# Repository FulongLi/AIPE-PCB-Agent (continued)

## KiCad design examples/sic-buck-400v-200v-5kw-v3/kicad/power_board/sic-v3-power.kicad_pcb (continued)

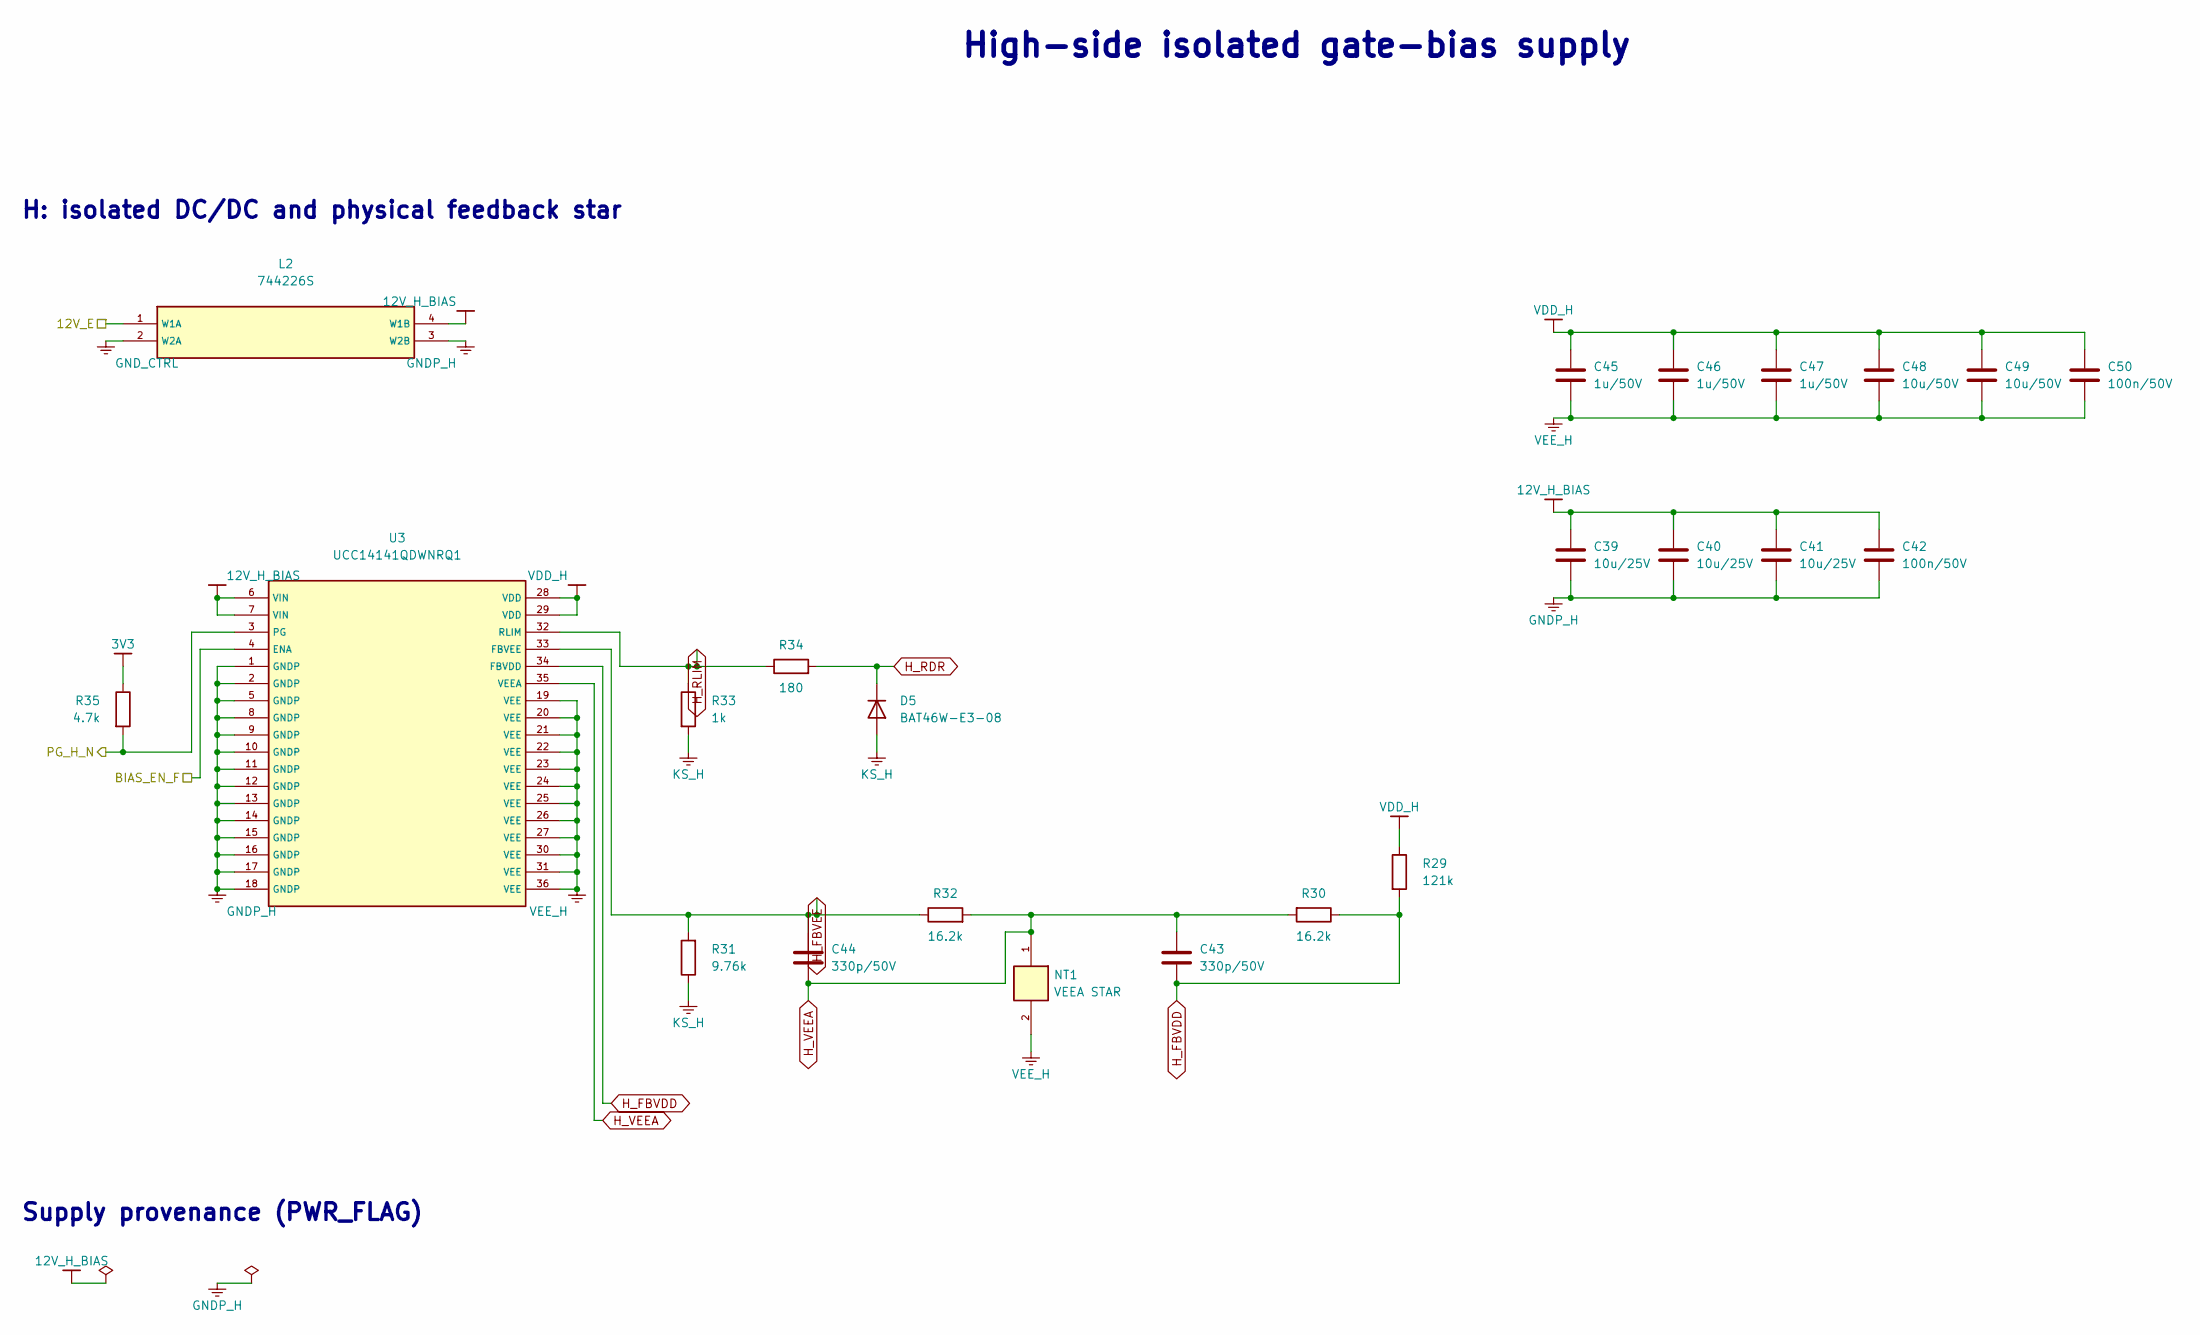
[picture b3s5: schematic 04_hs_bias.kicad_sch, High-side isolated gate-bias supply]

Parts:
C39, C40, C41: 10u/25V; C_1210_3225Metric
C42, C50: 100n/50V; C_0603_1608Metric
C43, C44: 330p/50V; C_0603_1608Metric
C45, C46, C47: 1u/50V; C_0805_2012Metric
C48, C49: 10u/50V; C_1210_3225Metric
D5: BAT46W-E3-08; D_SOD-123
L2: 744226S; L_CommonMode_Wuerth_WE-SL2
NT1: VEEA STAR; NetTie-2_SMD_Pad0.5mm
R29: 121k; R_0603_1608Metric
R30, R32: 16.2k; R_0603_1608Metric
R31: 9.76k; R_0603_1608Metric
R33: 1k; R_1206_3216Metric
R34: 180; R_1206_3216Metric
R35: 4.7k; R_0603_1608Metric
U3: UCC14141QDWNRQ1; V3_UCC14141_DWN

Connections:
3V3: R35.1; also elsewhere on the board
12V_E: L2.1 (W1A); also elsewhere on the board
12V_H_BIAS: C39.1, C40.1, C41.1, C42.1, L2.4 (W1B), U3.6 (VIN), U3.7 (VIN)
BIAS_EN_F: U3.4 (ENA); also elsewhere on the board
GNDP_H: C39.2, C40.2, C41.2, C42.2, L2.3 (W2B), U3.1 (GNDP), U3.2 (GNDP), U3.5 (GNDP), U3.8 (GNDP), U3.9 (GNDP), U3.10 (GNDP), U3.11 (GNDP), U3.12 (GNDP), U3.13 (GNDP), U3.14 (GNDP), U3.15 (GNDP), U3.16 (GNDP), U3.17 (GNDP), U3.18 (GNDP)
GND_CTRL: L2.2 (W2A); also elsewhere on the board
H_FBVDD: C43.1, R29.2, R30.1, U3.34 (FBVDD)
H_FBVEE: C44.1, R31.2, R32.1, U3.33 (FBVEE)
H_RDR: D5.1 (K), R34.2
H_RLIM: R33.1, R34.1, U3.32 (RLIM)
H_VEEA: C43.2, C44.2, NT1.1, R30.2, R32.2, U3.35 (VEEA)
KS_H: D5.2 (A), R31.1, R33.2; also elsewhere on the board
PG_H_N: R35.2, U3.3 (PG); also elsewhere on the board
VDD_H: C45.1, C46.1, C47.1, C48.1, C49.1, C50.1, R29.1, U3.28 (VDD), U3.29 (VDD); also elsewhere on the board
VEE_H: C45.2, C46.2, C47.2, C48.2, C49.2, C50.2, NT1.2, U3.19 (VEE), U3.20 (VEE), U3.21 (VEE), U3.22 (VEE), U3.23 (VEE), U3.24 (VEE), U3.25 (VEE), U3.26 (VEE), U3.27 (VEE), U3.30 (VEE), U3.31 (VEE), U3.36 (VEE); also elsewhere on the board

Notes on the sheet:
High-side isolated gate-bias supply
H: isolated DC/DC and physical feedback star
Supply provenance (PWR_FLAG)

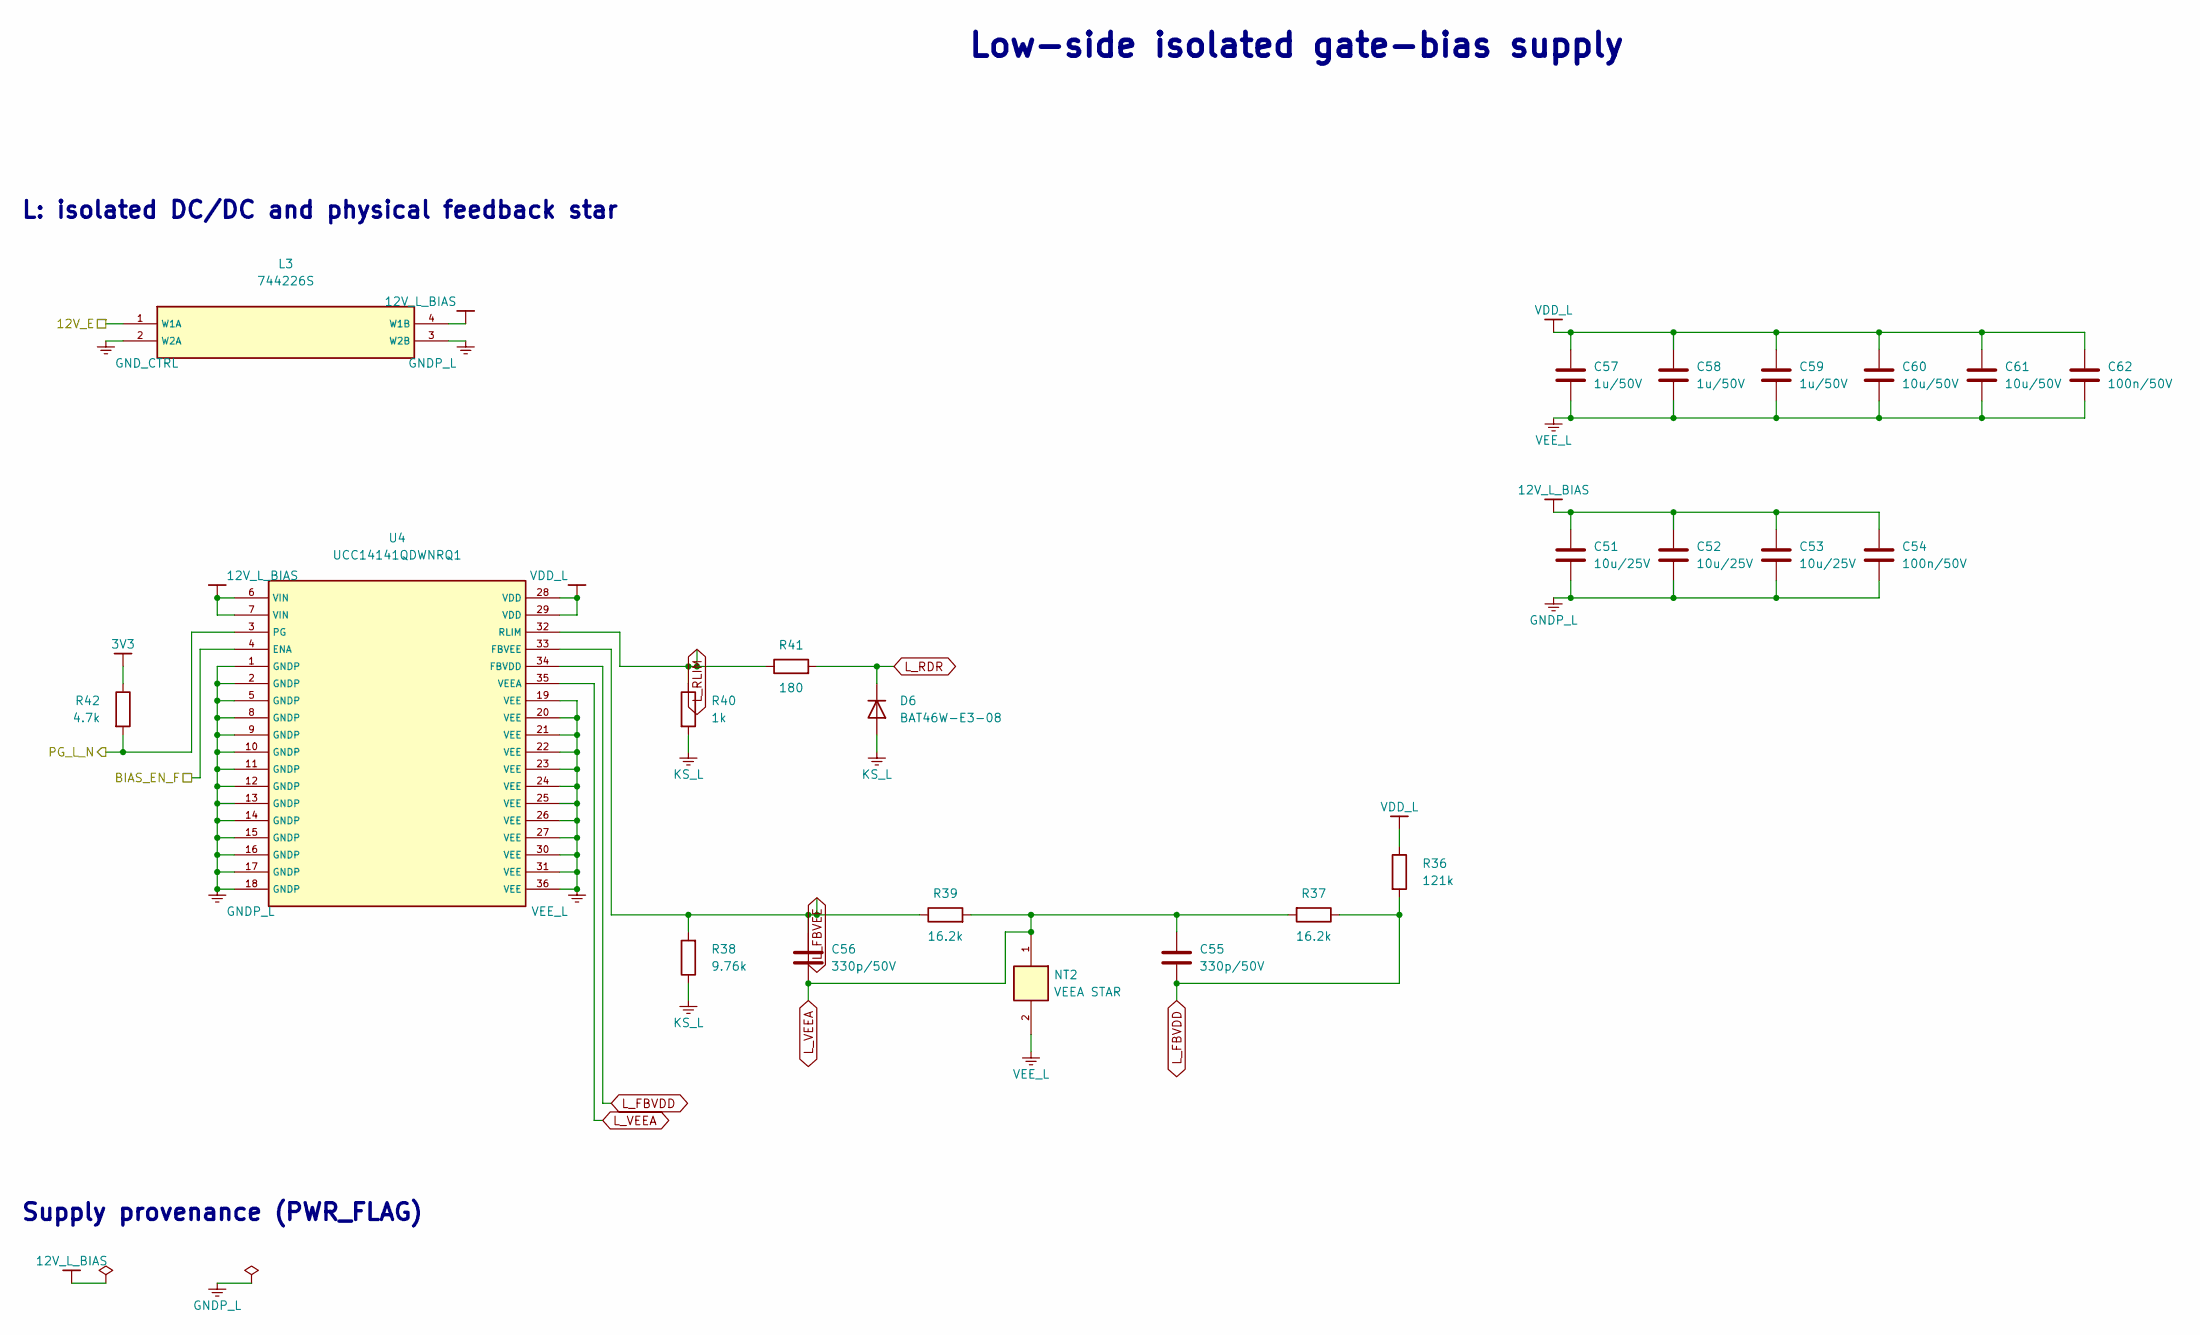
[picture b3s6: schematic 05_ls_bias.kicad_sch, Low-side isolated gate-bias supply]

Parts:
C51, C52, C53: 10u/25V; C_1210_3225Metric
C54, C62: 100n/50V; C_0603_1608Metric
C55, C56: 330p/50V; C_0603_1608Metric
C57, C58, C59: 1u/50V; C_0805_2012Metric
C60, C61: 10u/50V; C_1210_3225Metric
D6: BAT46W-E3-08; D_SOD-123
L3: 744226S; L_CommonMode_Wuerth_WE-SL2
NT2: VEEA STAR; NetTie-2_SMD_Pad0.5mm
R36: 121k; R_0603_1608Metric
R37, R39: 16.2k; R_0603_1608Metric
R38: 9.76k; R_0603_1608Metric
R40: 1k; R_1206_3216Metric
R41: 180; R_1206_3216Metric
R42: 4.7k; R_0603_1608Metric
U4: UCC14141QDWNRQ1; V3_UCC14141_DWN

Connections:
3V3: R42.1; also elsewhere on the board
12V_E: L3.1 (W1A); also elsewhere on the board
12V_L_BIAS: C51.1, C52.1, C53.1, C54.1, L3.4 (W1B), U4.6 (VIN), U4.7 (VIN)
BIAS_EN_F: U4.4 (ENA); also elsewhere on the board
GNDP_L: C51.2, C52.2, C53.2, C54.2, L3.3 (W2B), U4.1 (GNDP), U4.2 (GNDP), U4.5 (GNDP), U4.8 (GNDP), U4.9 (GNDP), U4.10 (GNDP), U4.11 (GNDP), U4.12 (GNDP), U4.13 (GNDP), U4.14 (GNDP), U4.15 (GNDP), U4.16 (GNDP), U4.17 (GNDP), U4.18 (GNDP)
GND_CTRL: L3.2 (W2A); also elsewhere on the board
KS_L: D6.2 (A), R38.1, R40.2; also elsewhere on the board
L_FBVDD: C55.1, R36.2, R37.1, U4.34 (FBVDD)
L_FBVEE: C56.1, R38.2, R39.1, U4.33 (FBVEE)
L_RDR: D6.1 (K), R41.2
L_RLIM: R40.1, R41.1, U4.32 (RLIM)
L_VEEA: C55.2, C56.2, NT2.1, R37.2, R39.2, U4.35 (VEEA)
PG_L_N: R42.2, U4.3 (PG); also elsewhere on the board
VDD_L: C57.1, C58.1, C59.1, C60.1, C61.1, C62.1, R36.1, U4.28 (VDD), U4.29 (VDD); also elsewhere on the board
VEE_L: C57.2, C58.2, C59.2, C60.2, C61.2, C62.2, NT2.2, U4.19 (VEE), U4.20 (VEE), U4.21 (VEE), U4.22 (VEE), U4.23 (VEE), U4.24 (VEE), U4.25 (VEE), U4.26 (VEE), U4.27 (VEE), U4.30 (VEE), U4.31 (VEE), U4.36 (VEE); also elsewhere on the board

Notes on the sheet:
Low-side isolated gate-bias supply
L: isolated DC/DC and physical feedback star
Supply provenance (PWR_FLAG)

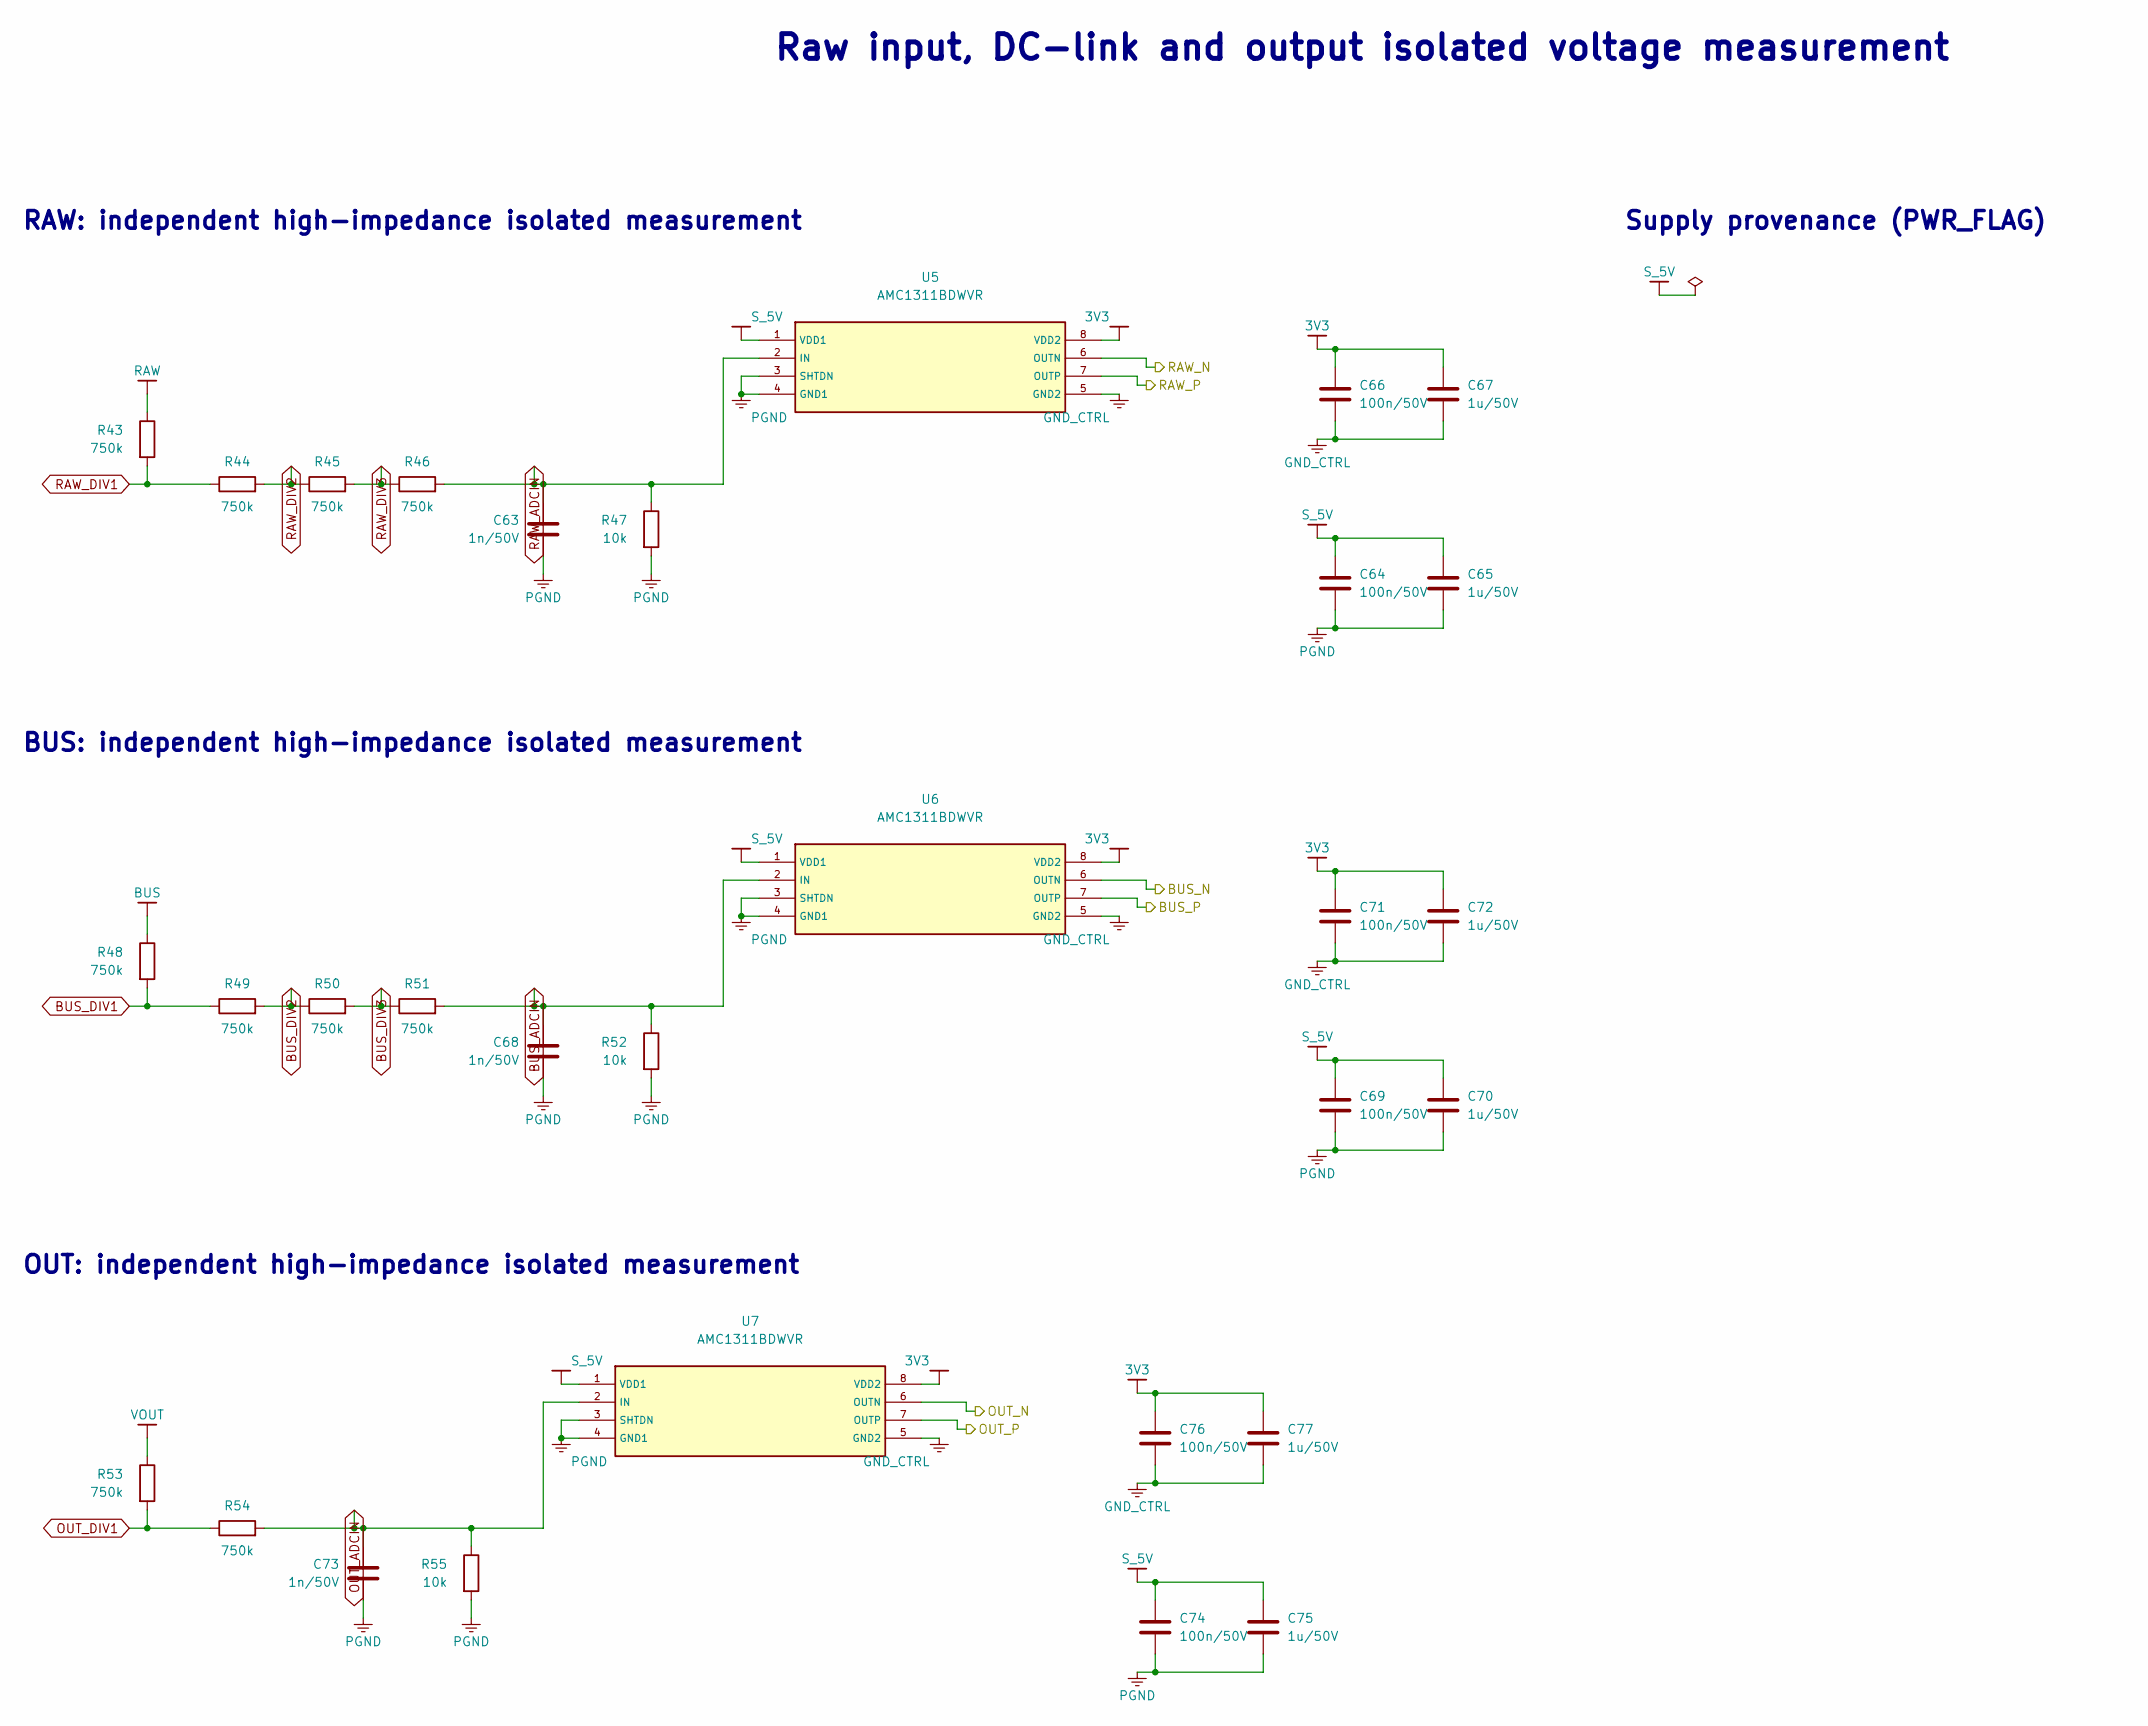
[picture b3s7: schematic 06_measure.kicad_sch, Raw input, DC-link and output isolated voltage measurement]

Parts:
C63, C68, C73: 1n/50V; C_0603_1608Metric
C64, C66, C69, C71, C74, C76: 100n/50V; C_0603_1608Metric
C65, C67, C70, C72, C75, C77: 1u/50V; C_0805_2012Metric
R43, R44, R45, R46, R48, R49, R50, R51, R53, R54: 750k; R_1206_3216Metric
R47, R52, R55: 10k; R_0603_1608Metric
U5, U6, U7: AMC1311BDWVR; V3_AMC1311_DWV

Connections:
3V3: C66.1, C67.1, C71.1, C72.1, C76.1, C77.1, U5.8 (VDD2), U6.8 (VDD2), U7.8 (VDD2); also elsewhere on the board
BUS: R48.1; also elsewhere on the board
BUS_ADCIN: C68.1, R51.2, R52.1, U6.2 (IN)
BUS_DIV1: R48.2, R49.1
BUS_DIV2: R49.2, R50.1
BUS_DIV3: R50.2, R51.1
BUS_N: U6.6 (OUTN); also elsewhere on the board
BUS_P: U6.7 (OUTP); also elsewhere on the board
GND_CTRL: C66.2, C67.2, C71.2, C72.2, C76.2, C77.2, U5.5 (GND2), U6.5 (GND2), U7.5 (GND2); also elsewhere on the board
OUT_ADCIN: C73.1, R54.2, R55.1, U7.2 (IN)
OUT_DIV1: R53.2, R54.1
OUT_N: U7.6 (OUTN); also elsewhere on the board
OUT_P: U7.7 (OUTP); also elsewhere on the board
PGND: C63.2, C64.2, C65.2, C68.2, C69.2, C70.2, C73.2, C74.2, C75.2, R47.2, R52.2, R55.2, U5.3 (SHTDN), U5.4 (GND1), U6.3 (SHTDN), U6.4 (GND1), U7.3 (SHTDN), U7.4 (GND1); also elsewhere on the board
RAW: R43.1; also elsewhere on the board
RAW_ADCIN: C63.1, R46.2, R47.1, U5.2 (IN)
RAW_DIV1: R43.2, R44.1
RAW_DIV2: R44.2, R45.1
RAW_DIV3: R45.2, R46.1
RAW_N: U5.6 (OUTN); also elsewhere on the board
RAW_P: U5.7 (OUTP); also elsewhere on the board
S_5V: C64.1, C65.1, C69.1, C70.1, C74.1, C75.1, U5.1 (VDD1), U6.1 (VDD1), U7.1 (VDD1); also elsewhere on the board
VOUT: R53.1; also elsewhere on the board

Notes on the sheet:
Raw input, DC-link and output isolated voltage measurement
RAW: independent high-impedance isolated measurement
BUS: independent high-impedance isolated measurement
OUT: independent high-impedance isolated measurement
Supply provenance (PWR_FLAG)

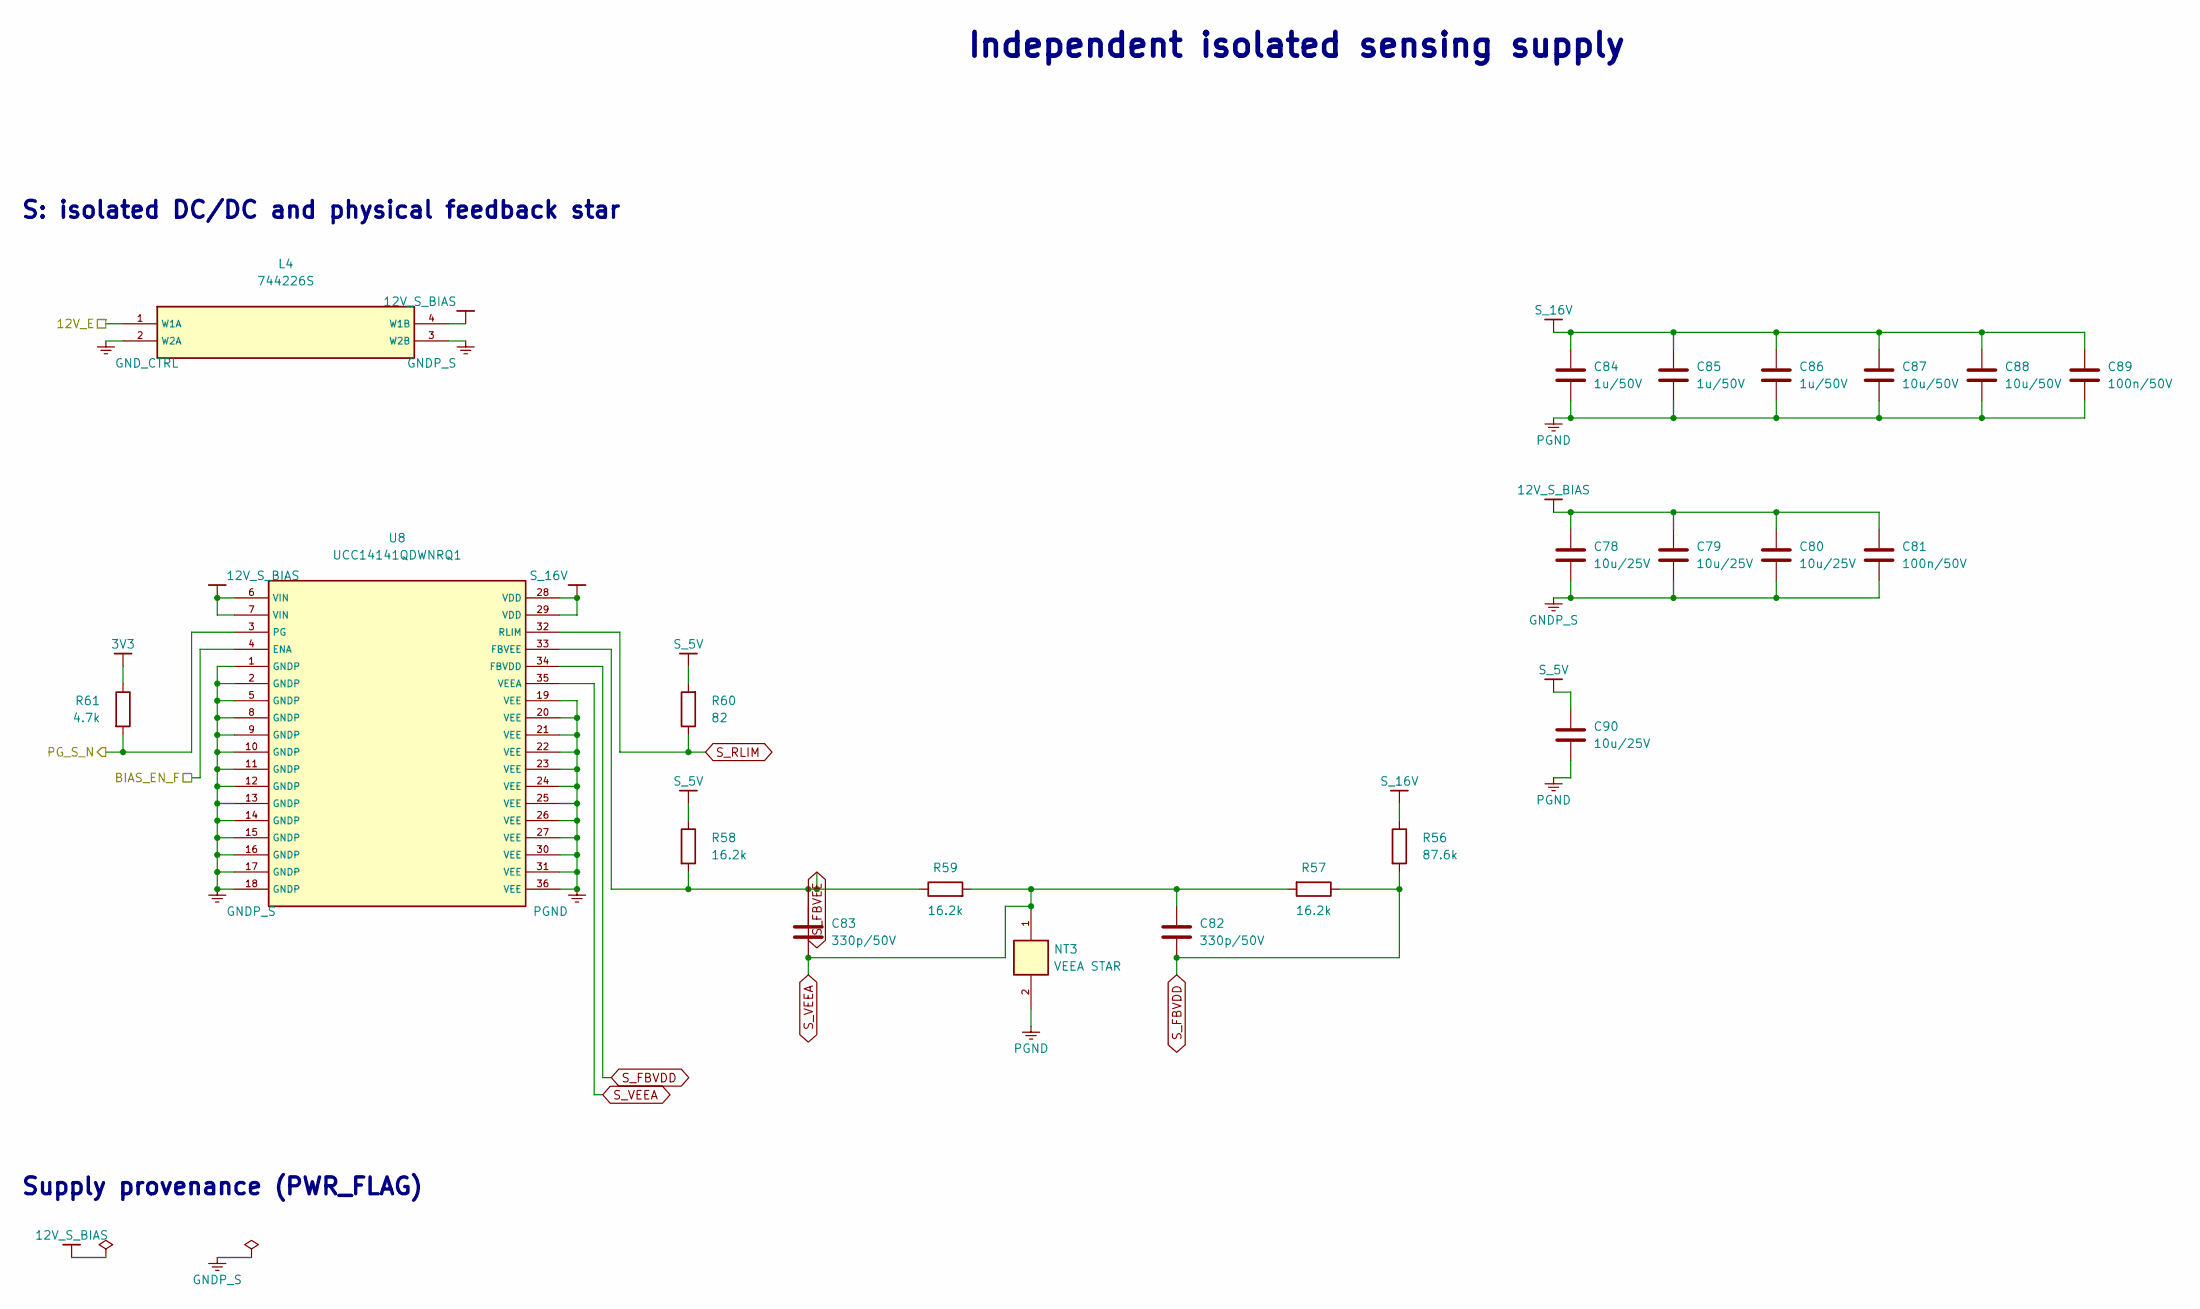
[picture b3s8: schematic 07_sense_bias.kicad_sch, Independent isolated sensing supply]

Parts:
C78, C79, C80, C90: 10u/25V; C_1210_3225Metric
C81, C89: 100n/50V; C_0603_1608Metric
C82, C83: 330p/50V; C_0603_1608Metric
C84, C85, C86: 1u/50V; C_0805_2012Metric
C87, C88: 10u/50V; C_1210_3225Metric
L4: 744226S; L_CommonMode_Wuerth_WE-SL2
NT3: VEEA STAR; NetTie-2_SMD_Pad0.5mm
R56: 87.6k; R_0603_1608Metric
R57, R58, R59: 16.2k; R_0603_1608Metric
R60: 82; R_1206_3216Metric
R61: 4.7k; R_0603_1608Metric
U8: UCC14141QDWNRQ1; V3_UCC14141_DWN

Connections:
3V3: R61.1; also elsewhere on the board
12V_E: L4.1 (W1A); also elsewhere on the board
12V_S_BIAS: C78.1, C79.1, C80.1, C81.1, L4.4 (W1B), U8.6 (VIN), U8.7 (VIN)
BIAS_EN_F: U8.4 (ENA); also elsewhere on the board
GNDP_S: C78.2, C79.2, C80.2, C81.2, L4.3 (W2B), U8.1 (GNDP), U8.2 (GNDP), U8.5 (GNDP), U8.8 (GNDP), U8.9 (GNDP), U8.10 (GNDP), U8.11 (GNDP), U8.12 (GNDP), U8.13 (GNDP), U8.14 (GNDP), U8.15 (GNDP), U8.16 (GNDP), U8.17 (GNDP), U8.18 (GNDP)
GND_CTRL: L4.2 (W2A); also elsewhere on the board
PGND: C84.2, C85.2, C86.2, C87.2, C88.2, C89.2, C90.2, NT3.2, U8.19 (VEE), U8.20 (VEE), U8.21 (VEE), U8.22 (VEE), U8.23 (VEE), U8.24 (VEE), U8.25 (VEE), U8.26 (VEE), U8.27 (VEE), U8.30 (VEE), U8.31 (VEE), U8.36 (VEE); also elsewhere on the board
PG_S_N: R61.2, U8.3 (PG); also elsewhere on the board
S_5V: C90.1, R58.1, R60.2; also elsewhere on the board
S_16V: C84.1, C85.1, C86.1, C87.1, C88.1, C89.1, R56.1, U8.28 (VDD), U8.29 (VDD)
S_FBVDD: C82.1, R56.2, R57.1, U8.34 (FBVDD)
S_FBVEE: C83.1, R58.2, R59.1, U8.33 (FBVEE)
S_RLIM: R60.1, U8.32 (RLIM)
S_VEEA: C82.2, C83.2, NT3.1, R57.2, R59.2, U8.35 (VEEA)

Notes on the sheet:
Independent isolated sensing supply
S: isolated DC/DC and physical feedback star
Supply provenance (PWR_FLAG)

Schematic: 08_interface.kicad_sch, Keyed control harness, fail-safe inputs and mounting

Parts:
C91, C92, C93, C94: 100p/50V; C_0603_1608Metric
C95: 10u/25V; C_1210_3225Metric
C96: 1u/50V; C_0805_2012Metric
H1, H2, H3, H4: M3 insulated standoff; MountingHole_3.2mm_M3
J7: POWER / CONTROL — 40-way; IDC-Header_2x20_P2.54mm_Vertical
R62, R64, R66, R68: 33; R_0603_1608Metric
R63, R65, R67, R69: 10k; R_0603_1608Metric

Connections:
3V3: C96.1, J7.37, J7.38; also elsewhere on the board
12V_E: C95.1, J7.33, J7.34; also elsewhere on the board
BIAS_EN: J7.8, R68.1
BIAS_EN_F: C94.1, R68.2, R69.1; also elsewhere on the board
BUS_N: J7.26; also elsewhere on the board
BUS_P: J7.25; also elsewhere on the board
DRV_RESET: J7.6, R66.1
DRV_RESET_F: C93.1, R66.2, R67.1; also elsewhere on the board
FLT_H_N: J7.10; also elsewhere on the board
FLT_L_N: J7.12; also elsewhere on the board
GND_CTRL: C91.2, C92.2, C93.2, C94.2, C95.2, C96.2, J7.1, J7.3, J7.5, J7.7, J7.9, J7.11, J7.13, J7.15, J7.17, J7.19, J7.21, J7.29, J7.31, J7.35, J7.36, J7.39, J7.40, R63.2, R65.2, R67.2, R69.2; also elsewhere on the board
OUT_N: J7.28; also elsewhere on the board
OUT_P: J7.27; also elsewhere on the board
PG_H_N: J7.18; also elsewhere on the board
PG_L_N: J7.20; also elsewhere on the board
PG_S_N: J7.22; also elsewhere on the board
PWM_H: J7.2, R62.1
PWM_H_F: C91.1, R62.2, R63.1; also elsewhere on the board
PWM_L: J7.4, R64.1
PWM_L_F: C92.1, R64.2, R65.1; also elsewhere on the board
RAW_N: J7.24; also elsewhere on the board
RAW_P: J7.23; also elsewhere on the board
RDY_H: J7.14; also elsewhere on the board
RDY_L: J7.16; also elsewhere on the board
TH_H_PWM: J7.30; also elsewhere on the board
TH_L_PWM: J7.32; also elsewhere on the board

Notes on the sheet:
Keyed control harness, fail-safe inputs and mounting
PWR_FLAG symbols state supply provenance for ERC; they do not prove voltage, current capacity or protection.
Keyed SELV cable and fail-safe receive inputs
Mechanical
Supply provenance (PWR_FLAG)

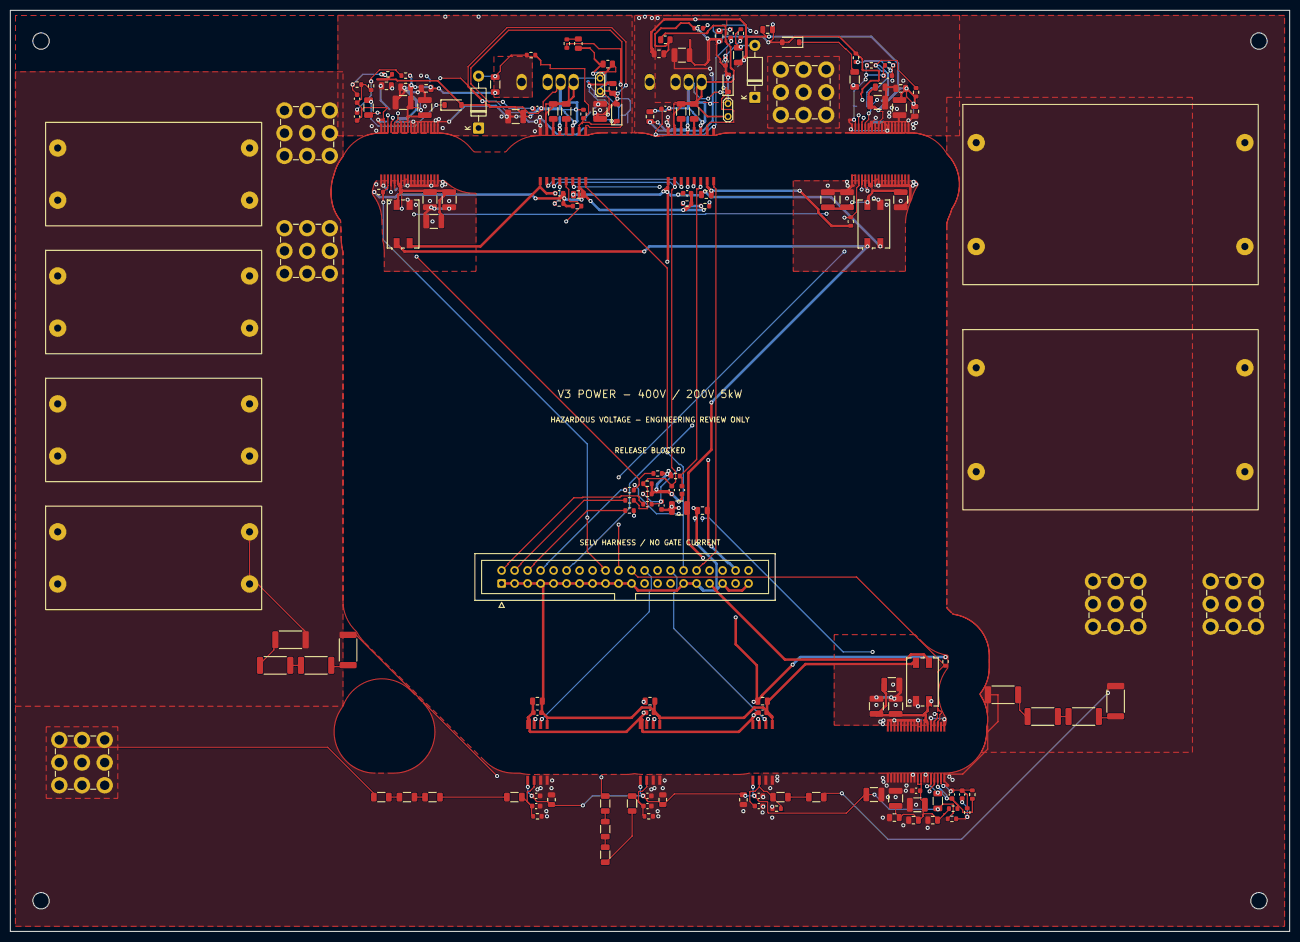
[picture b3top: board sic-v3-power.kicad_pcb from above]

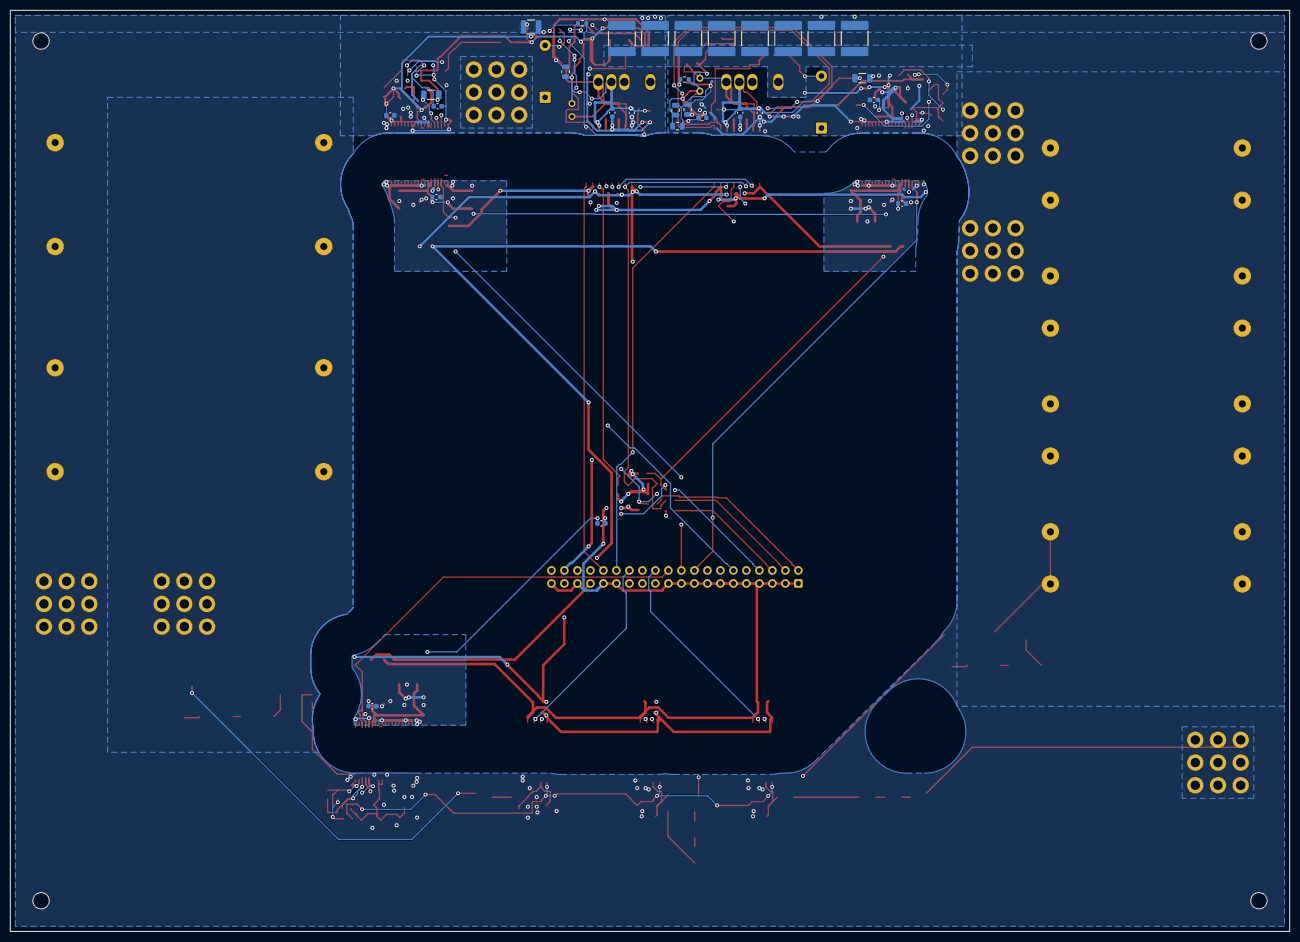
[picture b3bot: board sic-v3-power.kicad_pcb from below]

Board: 4 copper layers, 250.0 x 180.0 mm, 202 parts (29 on the bottom side), 89 nets.

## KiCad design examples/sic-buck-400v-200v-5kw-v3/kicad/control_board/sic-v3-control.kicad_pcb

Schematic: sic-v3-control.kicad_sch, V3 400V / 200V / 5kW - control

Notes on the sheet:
ENGINEERING PROTOTYPE REVIEW - RELEASE BLOCKED - NOT HARDWARE QUALIFIED
Independent V3 design; 360-440 V DC input; hazardous non-isolated 200 V output. Off-board choke, contactors and current sensor require the system assembly drawing.

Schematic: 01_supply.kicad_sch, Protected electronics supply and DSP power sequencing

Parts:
C1, C2, C5, C6, C12, C16: 100n/50V; C_0603_1608Metric
C3: 100u/25V; CP_Elec_8x10.5
C4: 10u/50V; C_1210_3225Metric
C7, C8, C11: 22u/25V; C_1210_3225Metric
C9: 220u; CP_Radial_D6.3mm_P2.50mm
C10: 100p/50V; C_0603_1608Metric
C13, C14: 100u; CP_Elec_6.3x5.9
C15: 10n/50V; C_0603_1608Metric
D1: SMBJ15A; D_SMB
D2: BAT46W-E3-08; D_SOD-123
J1: 12 V ELECTRONICS; TerminalBlock_Phoenix_MKDS-1,5-2-5.08_1x02_P5.08mm_Horizont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
J2: RESET input; PinHeader_1x02_P2.54mm_Vertical
L1: 10uH; L_Coilcraft_MSS1048-XXX
Q1: MMBT3904,215; SOT-23
R1: 107k; R_0603_1608Metric
R2: 4.42k; R_0603_1608Metric
R3, R7, R14, R15, R16, R21: 10k; R_0603_1608Metric
R4: 6.04k; R_0603_1608Metric
R5: 14.7k; R_0603_1608Metric
R6, R8, R10, R17: 100k; R_0603_1608Metric
R9: 20k; R_0603_1608Metric
R11: 13.3k; R_0603_1608Metric
R12: 18.2k; R_0603_1608Metric
R13: 30.1k; R_0603_1608Metric
R18, R19: 0.1; R_0805_2012Metric
R20: 101k; R_0603_1608Metric
R22: 4.7k; R_0603_1608Metric
TP1: E_IMON; TestPoint_Pad_D1.0mm
U1: TPS26400PWPR; HTSSOP-16-1EP_4.4x5mm_P0.65mm_EP3.4x5mm
U2: TPS54302DDCR; SOT-23-6
U3: TPS767D301PWPR; HTSSOP-28-1EP_4.4x9.7mm_P0.65mm_EP2.85x5.4mm
U4: TPS3808G01DBVR; SOT-23-6

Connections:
1V9: R12.1, R18.1, U3.23 (1OUT), U3.24 (1OUT); also elsewhere on the board
1V9_BULK: C13.1, R18.2
3V3: C16.1, R7.1, R19.1, R22.1, U3.17 (2OUT), U3.18 (2OUT), U4.6 (VDD); also elsewhere on the board
3V3_BULK: C14.1, R19.2
5V: C7.1, C8.1, C9.1, C10.1, C11.1, C12.1, L1.2, R10.1, R14.1, R15.1, R20.1, U3.5 (1IN), U3.6 (1IN), U3.11 (2IN), U3.12 (2IN); also elsewhere on the board
12V_E: C3.1, C4.1, C5.1, R8.1, U1.15 (OUT), U1.16 (OUT), U2.3 (VIN); also elsewhere on the board
12V_IN: C2.1, D1.1 (K), J1.1, R1.1, R6.1, U1.1 (IN), U1.2 (IN)
AUX_OK_N: R7.2, U1.14 (FLT); also elsewhere on the board
BST5: C6.1, U2.6 (BOOT)
CORE_OK: D2.1 (K), R14.2, R16.1, U3.28 (1RESET_N)
EN5: R8.2, R9.1, U2.5 (EN)
E_DVDT: C1.1, U1.12 (dVdT)
E_EN: R6.2, U1.7 (SHDN)
E_ILIM: R4.1, U1.11 (ILIM)
E_IMON: R5.1, TP1.1, U1.10 (IMON)
E_OV: R2.2, R3.1, U1.5 (OVP)
E_RTN: C1.2, R3.2, R4.2, R5.2, U1.8 (RTN), U1.17 (PAD)
E_UV: R1.2, R2.1, U1.3 (UVLO)
FB5: C10.2, R10.2, R11.1, U2.4 (FB)
FB19: R12.2, R13.1, U3.25 (1FB)
GND_CTRL: C2.2, C3.2, C4.2, C5.2, C7.2, C8.2, C9.2, C11.2, C12.2, C13.2, C14.2, C15.2, C16.2, D1.2 (A), J1.2, J2.2, Q1.2 (E), R9.2, R11.2, R13.2, R17.2, R21.2, U1.9 (GND), U2.1 (GND), U3.3 (1GND), U3.4 (1EN_N), U3.9 (2GND), U3.29 (EP), U4.2 (GND); also elsewhere on the board
IO_EN_N: Q1.3 (C), R15.2, U3.10 (2EN_N)
MON5: R20.2, R21.1, U4.5 (SENSE)
MR_N: J2.1, U4.3 (MR_N)
RESET_CT: C15.1, U4.4 (CT)
SEQ_B: Q1.1 (B), R16.2, R17.1
SW5: C6.2, L1.1, U2.2 (SW)
XRS_N: D2.2 (A), R22.2, U3.22 (2RESET_N), U4.1 (RESET_N); also elsewhere on the board

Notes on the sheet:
Protected electronics supply and DSP power sequencing
PWR_FLAG symbols state supply provenance for ERC; they do not prove voltage, current capacity or protection.
12 V electronics entry: independent 2 A protection
5 V logic / sensor buck supply
Core-first 1.9 V / 3.3 V supply sequencing
Supply supervisor; reset also clears the hardware latch
Supply provenance (PWR_FLAG)
